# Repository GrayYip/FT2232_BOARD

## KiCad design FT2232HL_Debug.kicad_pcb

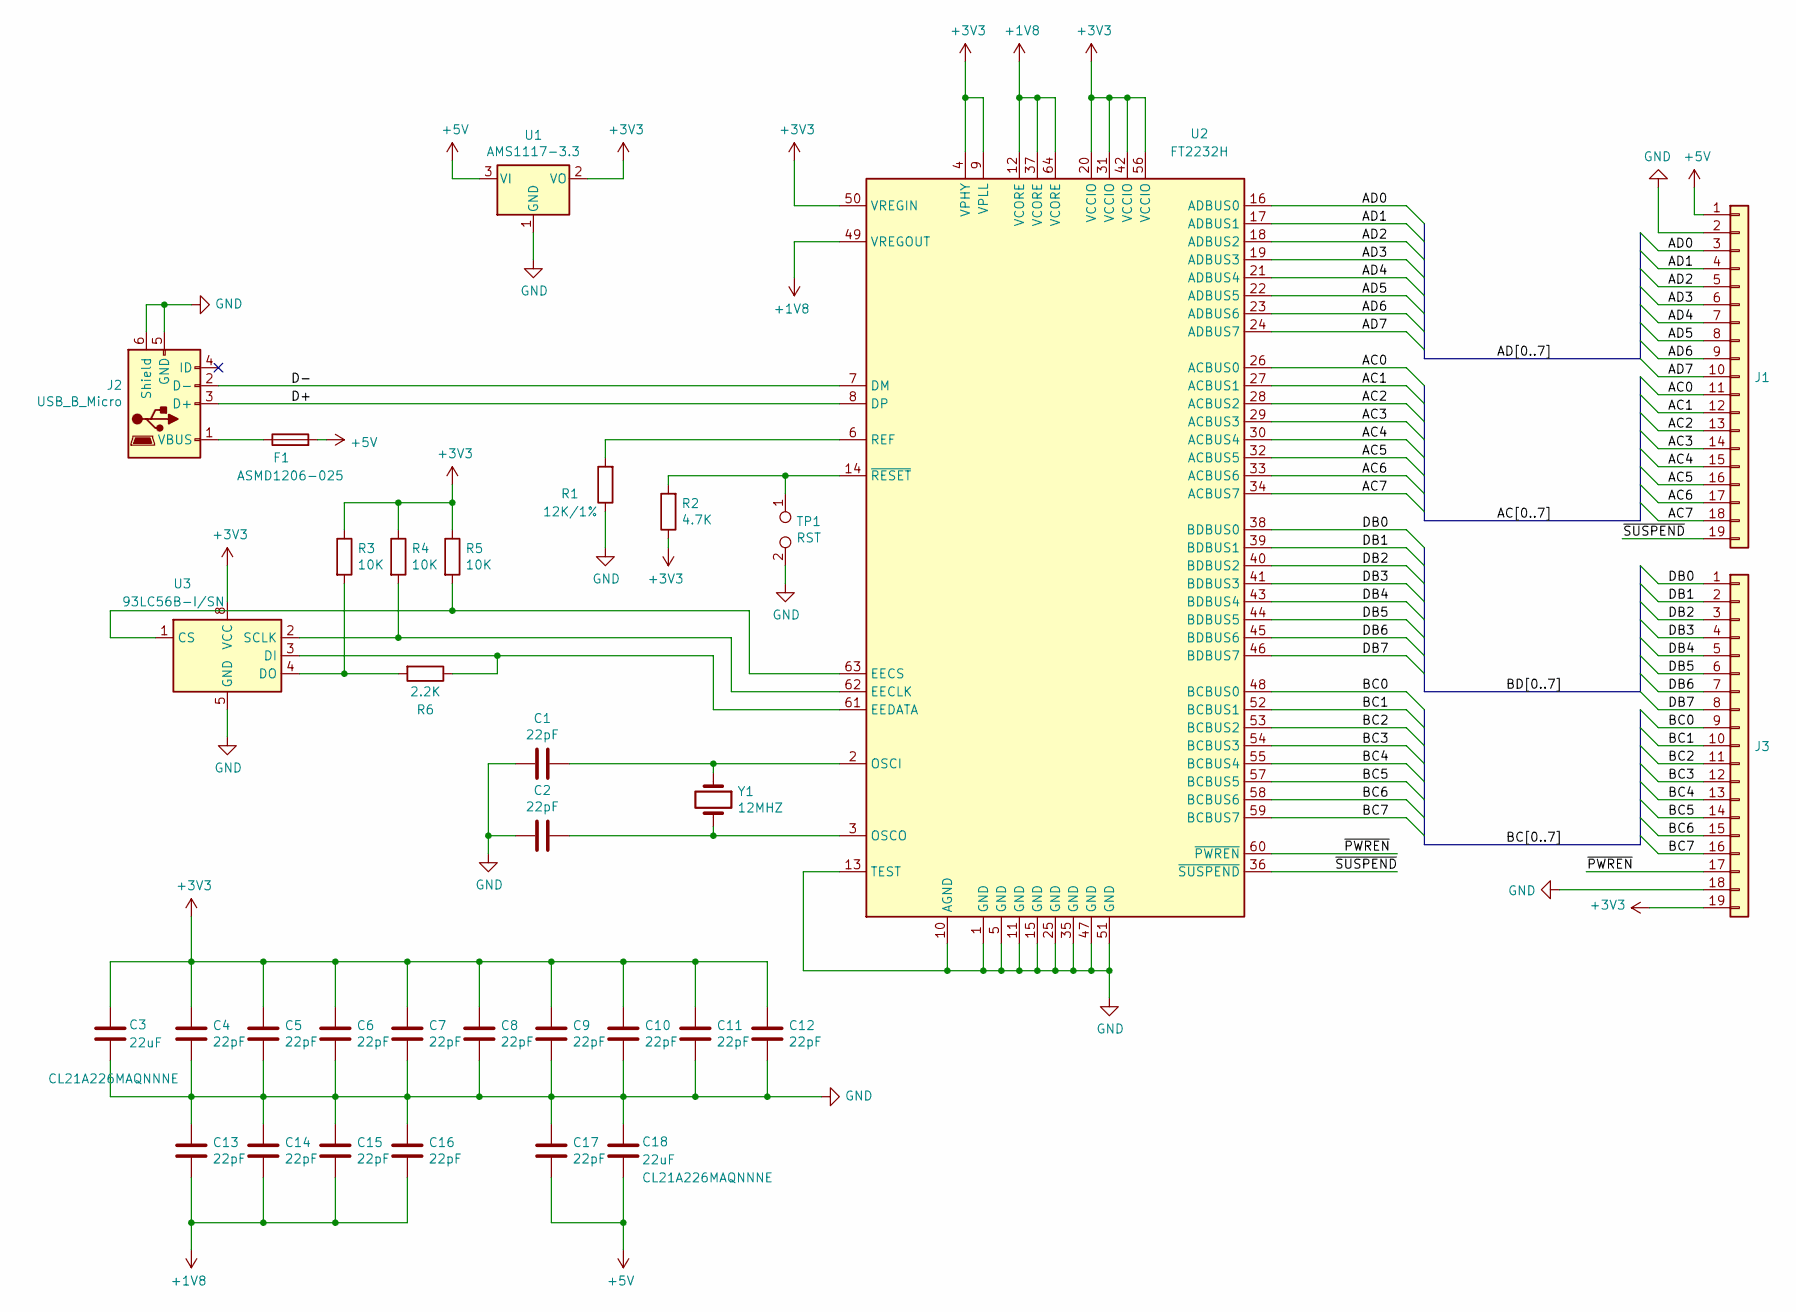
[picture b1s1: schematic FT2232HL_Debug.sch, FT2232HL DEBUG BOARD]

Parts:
C1, C2, C4, C5, C6, C7, C8, C9, C10, C11, C12, C13, C14, C15, C16, C17: 22pF; C_0603_1608Metric_Pad1.05x0.95mm_HandSolder
C3, C18: 22uF; C_0805_2012Metric_Pad1.15x1.40mm_HandSolder
F1: ASMD1206-025; Fuse_1206_3216Metric_Pad1.42x1.75mm_HandSolder
J1, J3: Conn_01x19; PinHeader_1x19_P2.54mm_Vertical
J2: USB_B_Micro; USB_MICRO_B_SHOU_HAN
R1: 12K/1%; R_0603_1608Metric_Pad1.05x0.95mm_HandSolder
R2: 4.7K; R_0603_1608Metric_Pad1.05x0.95mm_HandSolder
R3, R4, R5: 10K; R_0603_1608Metric_Pad1.05x0.95mm_HandSolder
R6: 2.2K; R_0603_1608Metric_Pad1.05x0.95mm_HandSolder
TP1: RST; TestPoint_2Pads_Pitch2.54mm_Drill0.8mm
U1: AMS1117-3.3; SOT-223-3_TabPin2
U2: FT2232H; LQFP-64_10x10mm_P0.5mm
U3: 93LC56B-I/SN; SOIC-8_3.9x4.9mm_P1.27mm
Y1: 12MHZ; Crystal_SMD_5032-2Pin_5.0x3.2mm_HandSoldering

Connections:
+1V8: C13.2, C14.2, C15.2, C16.2, U2.12 (VCORE), U2.37 (VCORE), U2.49 (VREGOUT), U2.64 (VCORE)
+3V3: C3.1, C4.1, C5.1, C6.1, C7.1, C8.1, C9.1, C10.1, C11.1, C12.1, J3.19, R2.1, R3.1, R4.1, R5.1, U1.2 (VO), U2.4 (VPHY), U2.9 (VPLL), U2.20 (VCCIO), U2.31 (VCCIO), U2.42 (VCCIO), U2.50 (VREGIN), U2.56 (VCCIO), U3.8 (VCC)
+5V: C17.2, C18.2, F1.2, J1.1, U1.3 (VI)
/AC0: J1.11, U2.26 (ACBUS0)
/AC1: J1.12, U2.27 (ACBUS1)
/AC2: J1.13, U2.28 (ACBUS2)
/AC3: J1.14, U2.29 (ACBUS3)
/AC4: J1.15, U2.30 (ACBUS4)
/AC5: J1.16, U2.32 (ACBUS5)
/AC6: J1.17, U2.33 (ACBUS6)
/AC7: J1.18, U2.34 (ACBUS7)
/AD0: J1.3, U2.16 (ADBUS0)
/AD1: J1.4, U2.17 (ADBUS1)
/AD2: J1.5, U2.18 (ADBUS2)
/AD3: J1.6, U2.19 (ADBUS3)
/AD4: J1.7, U2.21 (ADBUS4)
/AD5: J1.8, U2.22 (ADBUS5)
/AD6: J1.9, U2.23 (ADBUS6)
/AD7: J1.10, U2.24 (ADBUS7)
/BC0: J3.9, U2.48 (BCBUS0)
/BC1: J3.10, U2.52 (BCBUS1)
/BC2: J3.11, U2.53 (BCBUS2)
/BC3: J3.12, U2.54 (BCBUS3)
/BC4: J3.13, U2.55 (BCBUS4)
/BC5: J3.14, U2.57 (BCBUS5)
/BC6: J3.15, U2.58 (BCBUS6)
/BC7: J3.16, U2.59 (BCBUS7)
/D+: J2.3 (D+), U2.8 (DP)
/D-: J2.2 (D-), U2.7 (DM)
/DB0: J3.1, U2.38 (BDBUS0)
/DB1: J3.2, U2.39 (BDBUS1)
/DB2: J3.3, U2.40 (BDBUS2)
/DB3: J3.4, U2.41 (BDBUS3)
/DB4: J3.5, U2.43 (BDBUS4)
/DB5: J3.6, U2.44 (BDBUS5)
/DB6: J3.7, U2.45 (BDBUS6)
/DB7: J3.8, U2.46 (BDBUS7)
/~PWREN: J3.17, U2.60 (~PWREN)
/~SUSPEND: J1.19, U2.36 (~SUSPEND)
GND: C1.2, C2.2, C3.2, C4.2, C5.2, C6.2, C7.2, C8.2, C9.2, C10.2, C11.2, C12.2, C13.1, C14.1, C15.1, C16.1, C17.1, C18.1, J1.2, J2.5 (GND), J2.6 (Shield), J3.18, R1.1, TP1.2, U1.1 (GND), U2.1 (GND), U2.5 (GND), U2.10 (AGND), U2.11 (GND), U2.13 (TEST), U2.15 (GND), U2.25 (GND), U2.35 (GND), U2.47 (GND), U2.51 (GND), U3.5 (GND)
unnamed: C1.1, U2.2 (OSCI), Y1.1
unnamed: C2.1, U2.3 (OSCO), Y1.2
unnamed: F1.1, J2.1 (VBUS)
unnamed: R1.2, U2.6 (REF)
unnamed: R2.2, TP1.1, U2.14 (~RESET)
unnamed: R3.2, R6.2, U3.4 (DO)
unnamed: R4.2, U2.62 (EECLK), U3.2 (SCLK)
unnamed: R5.2, U2.63 (EECS), U3.1 (CS)
unnamed: R6.1, U2.61 (EEDATA), U3.3 (DI)

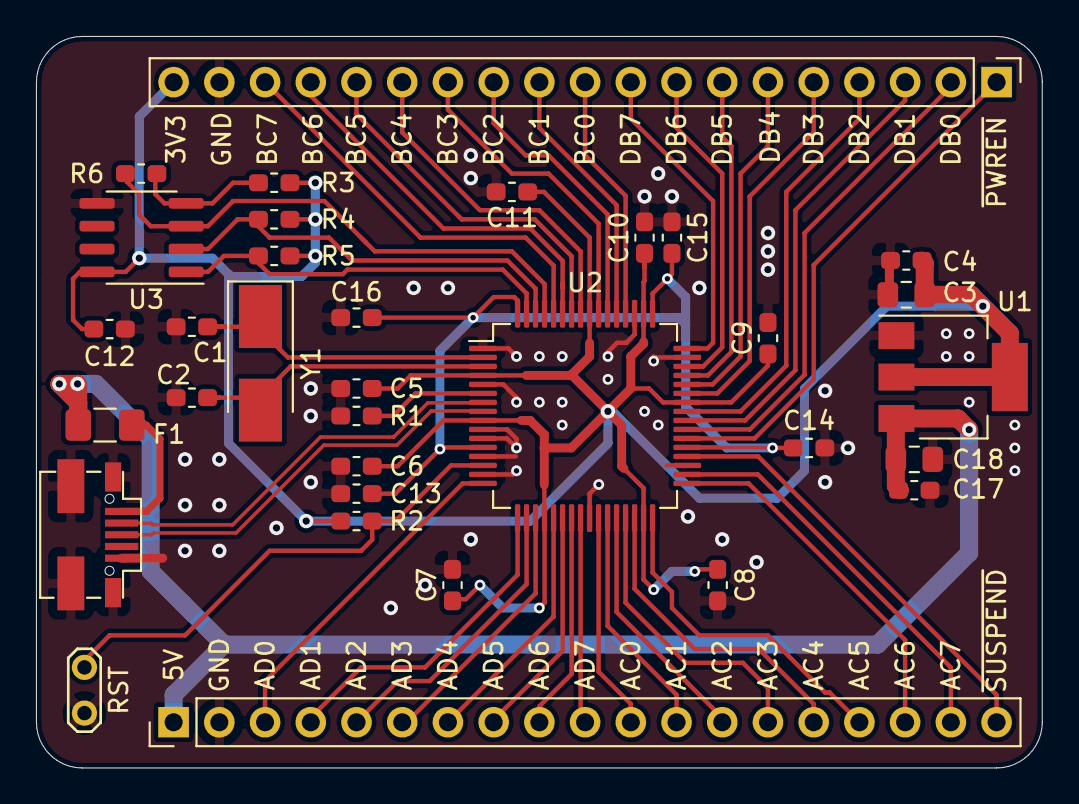
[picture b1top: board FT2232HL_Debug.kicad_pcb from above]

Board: 2 copper layers, 55.9 x 40.6 mm, 33 parts (0 on the bottom side), 49 nets.

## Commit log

2020-01-16 新文件： .gitignore 新文件： FT2232HL_Debug-cache.lib 新文件： FT2232HL_Debug.csv 新文件： FT2232HL_Debug.kicad_pcb 新文件： FT2232HL_Debug.net 新文件： FT2232HL_Debug.pdf 新文件： FT2232HL_Debug.pro 新文件： FT2232HL_Debug.sch 新文件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
2020-01-16 新文件： README
